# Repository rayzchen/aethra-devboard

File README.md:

# aethra-devboard
Custom devboard based on the RP2040 chip. Includes LiPo 3.7V battery charger and
power source selector, onboard neopixel LED, 16MB flash storage and 29 GPIO
pins.

## Schematic

## PCB

## BOM
|Comment                    |Footprint                                       |LCSC Part No|Quantity|Link                                                 |Price/unit |Total |
|---------------------------|------------------------------------------------|------------|--------|-----------------------------------------------------|-----------|------|
|AP2112K-3.3                |SOT-23-5                                        |C23380830   |1       |https://www.lcsc.com/product-detail/C23380830.html   |0.0975     |0.0975|
|RP2040                     |QFN-56-1EP_7x7mm_P0.4mm_EP3.2x3.2mm             |C2040       |1       |https://www.lcsc.com/product-detail/C2040.html       |0.9577     |0.9577|
|33pF                       |C_0402_1005Metric                               |C1562       |2       |https://www.lcsc.com/product-detail/C1562.html       |0.0011     |0.0022|
|0.1uF                      |C_0402_1005Metric                               |C1525       |11      |https://www.lcsc.com/product-detail/C1525.html       |0.0013     |0.0143|
|10K                        |R_0402_1005Metric                               |C25744      |4       |https://www.lcsc.com/product-detail/C25744.html      |0.0007     |0.0028|
|1uF                        |C_0402_1005Metric                               |C52923      |2       |https://www.lcsc.com/product-detail/C52923.html      |0.0032     |0.0064|
|1K                         |R_0402_1005Metric                               |C11702      |2       |https://www.lcsc.com/product-detail/C11702.html      |0.0006     |0.0012|
|Conn_01x02                 |JST_PH_S2B-PH-SM4-TB_1x02-1MP_P2.00mm_Horizontal|C295747     |1       |https://www.lcsc.com/product-detail/C295747.html     |0.1877     |0.1877|
|27                         |R_0402_1005Metric                               |C138021     |2       |https://www.lcsc.com/product-detail/C138021.html     |0.0008     |0.0016|
|12 MHz                     |Crystal_SMD_3225-4Pin_3.2x2.5mm                 |C9002       |1       |https://www.lcsc.com/product-detail/C9002.html       |0.0681     |0.0681|
|W25Q16JVZPIQ               |Winbond_USON-8-1EP_3x2mm_P0.5mm_EP0.2x1.6mm     |C377853     |1       |https://www.lcsc.com/product-detail/C377853.html     |1.0674     |1.0674|
|USB_C_Receptacle_USB2.0_14P|USB_C_Receptacle_HRO_TYPE-C-31-M-12             |C165948     |1       |https://www.lcsc.com/product-detail/C165948.html     |0.1772     |0.1772|
|LED                        |LED_0402_1005Metric                             |C130719     |1       |https://www.lcsc.com/product-detail/C130719.html     |0.0369     |0.0369|
|10uF                       |C_0402_1005Metric                               |C15525      |3       |https://www.lcsc.com/product-detail/C15525.html      |0.005      |0.015 |
|Conn_01x03                 |JST_SH_BM03B-SRSS-TB_1x03-1MP_P1.00mm_Vertical  |C160389     |1       |https://www.lcsc.com/product-detail/C160389.html     |0.2576     |0.2576|
|DMG2301L                   |SOT-23                                          |C102619     |1       |https://www.lcsc.com/product-detail/C102619.html     |0.07       |0.07  |
|5.1K                       |R_0402_1005Metric                               |C25905      |3       |https://www.lcsc.com/product-detail/C25905.html      |0.0006     |0.0018|
|MCP73831-2-OT              |SOT-23-5                                        |C424093     |1       |https://www.lcsc.com/product-detail/C424093.html     |0.7226     |0.7226|
|MBR0540                    |D_SOD-123                                       |C116159     |1       |https://www.lcsc.com/product-detail/C116159.html     |0.0204     |0.0204|
|SW_Push                    |SW_Push_SPST_NO_Alps_SKRK                       |C720477     |1       |https://www.lcsc.com/product-detail/C720477.html     |0.0444     |0.0444|
|Conn_01x20                 |PinHeader_1x20_P2.54mm_Vertical                 |            |2       |https://www.aliexpress.com/item/4001053521664.html   |1.255      |2.51  |
|SK6805                     |LED_SK6805_PLCC4_2.4x2.7mm_P1.3mm               |            |1       |https://www.aliexpress.com/item/1005008719791221.html|1.37       |1.37  |
|                           |                                                |            |        |                                                     |Grand Total|7.6328|

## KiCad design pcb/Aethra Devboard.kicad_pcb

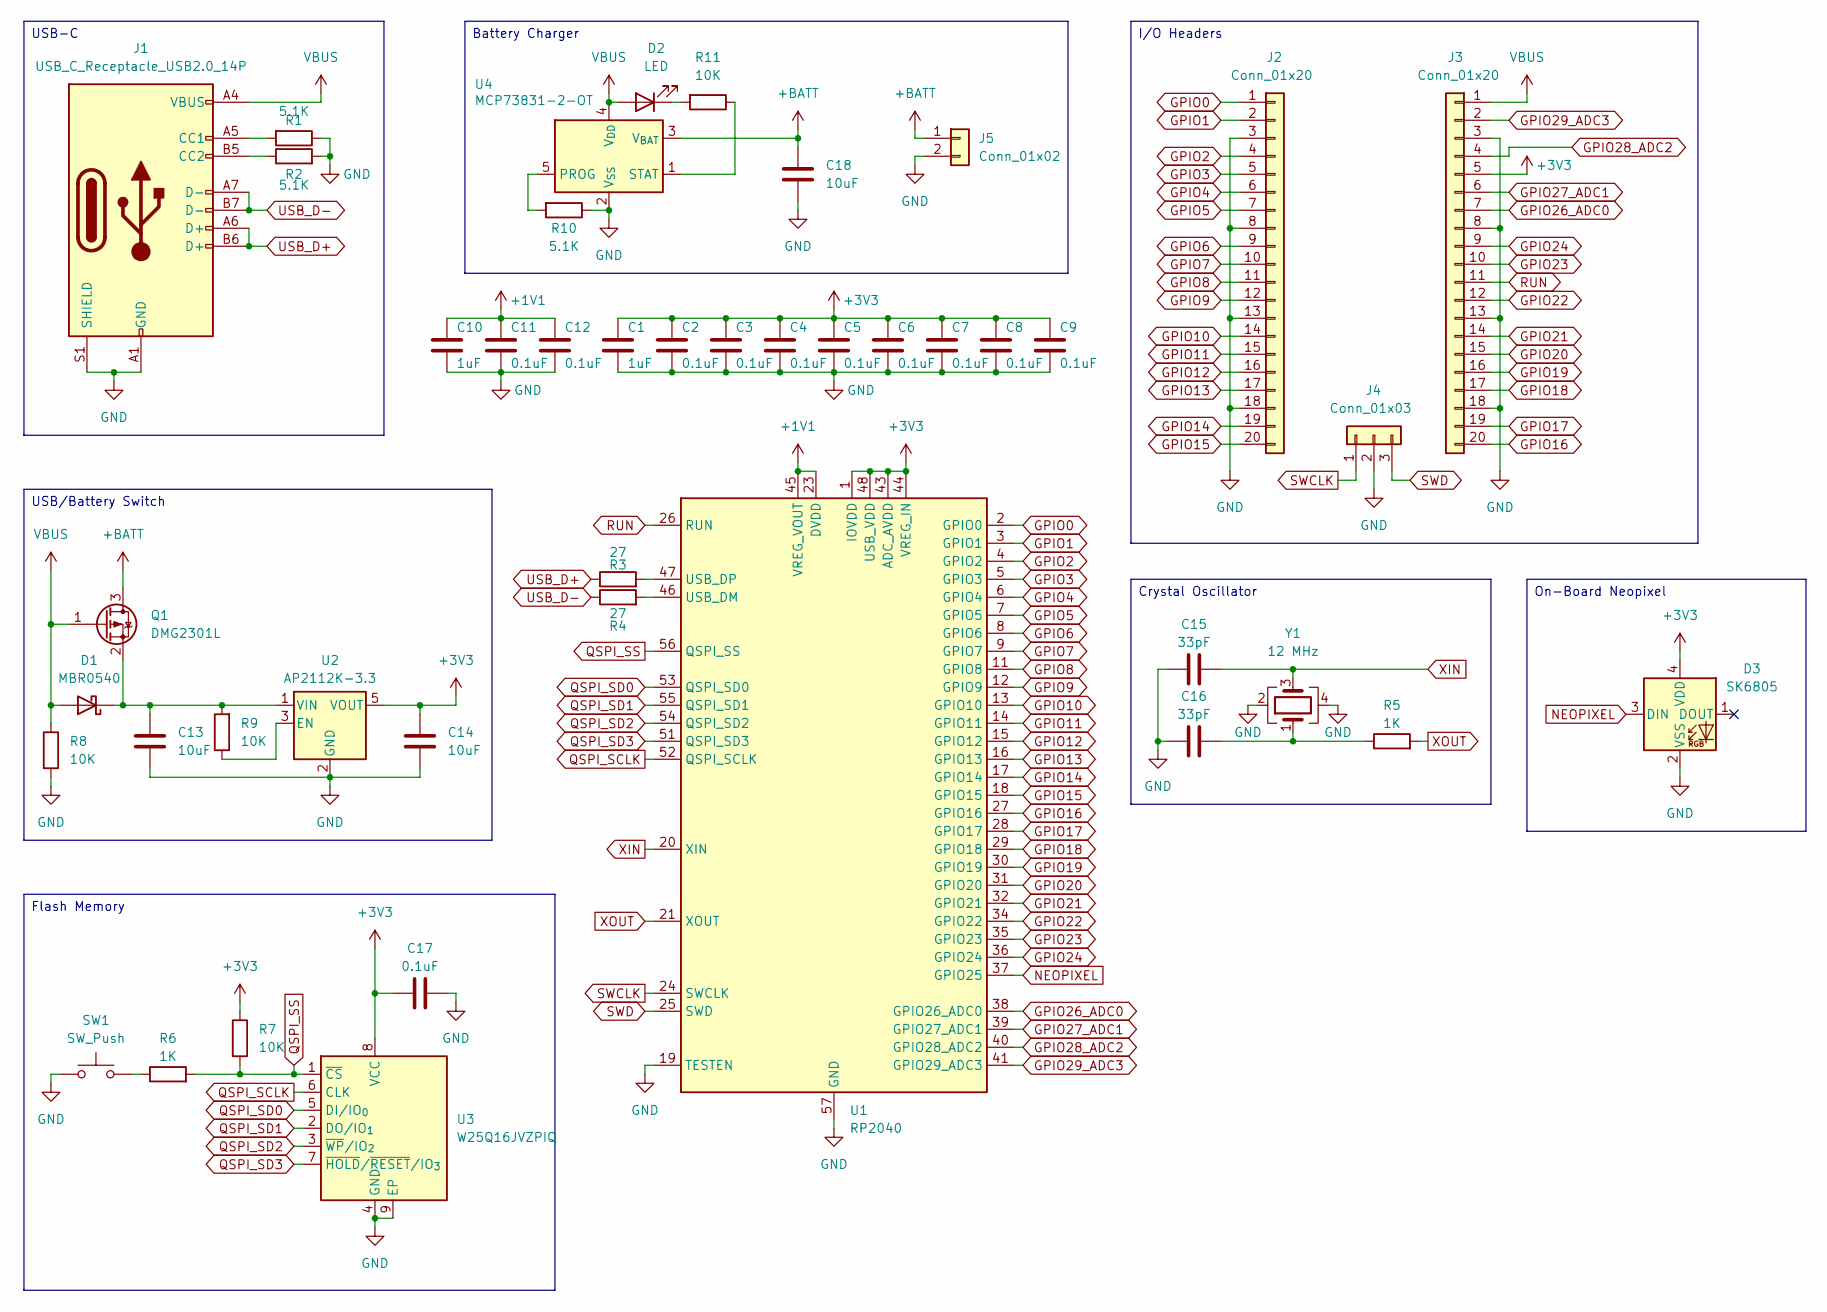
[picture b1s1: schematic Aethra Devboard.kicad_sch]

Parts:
C1, C10: 1uF; C_0402_1005Metric
C2, C3, C4, C5, C6, C7, C8, C9, C11, C12, C17: 0.1uF; C_0402_1005Metric
C13, C14, C18: 10uF; C_0402_1005Metric
C15, C16: 33pF; C_0402_1005Metric
D1: MBR0540; D_SOD-123
D2: LED; LED_0402_1005Metric
D3: SK6805; LED_SK6805_PLCC4_2.4x2.7mm_P1.3mm
J1: USB_C_Receptacle_USB2.0_14P; USB_C_Receptacle_HRO_TYPE-C-31-M-12
J2, J3: Conn_01x20; PinHeader_1x20_P2.54mm_Vertical
J4: Conn_01x03; JST_SH_BM03B-SRSS-TB_1x03-1MP_P1.00mm_Vertical
J5: Conn_01x02; JST_PH_S2B-PH-SM4-TB_1x02-1MP_P2.00mm_Horizontal
Q1: DMG2301L; SOT-23
R1, R2, R10: 5.1K; R_0402_1005Metric
R3, R4: 27; R_0402_1005Metric
R5, R6: 1K; R_0402_1005Metric
R7, R8, R9, R11: 10K; R_0402_1005Metric
SW1: SW_Push; SW_Push_SPST_NO_Alps_SKRK
U1: RP2040; QFN-56-1EP_7x7mm_P0.4mm_EP3.2x3.2mm
U2: AP2112K-3.3; SOT-23-5
U3: W25Q16JVZPIQ; Winbond_USON-8-1EP_3x2mm_P0.5mm_EP0.2x1.6mm
U4: MCP73831-2-OT; SOT-23-5
Y1: 12 MHz; Crystal_SMD_3225-4Pin_3.2x2.5mm

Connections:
+1V1: C10.1, C11.1, C12.1, U1.23 (DVDD), U1.45 (VREG_VOUT), U1.50 (DVDD)
+3V3: C1.1, C2.1, C3.1, C4.1, C5.1, C6.1, C7.1, C8.1, C9.1, C14.1, C17.1, D3.4 (VDD), J3.5, R7.1, U1.1 (IOVDD), U1.10 (IOVDD), U1.22 (IOVDD), U1.33 (IOVDD), U1.42 (IOVDD), U1.43 (ADC_AVDD), U1.44 (VREG_IN), U1.48 (USB_VDD), U1.49 (IOVDD), U2.5 (VOUT), U3.8 (VCC)
+BATT: C18.1, J5.1, Q1.3 (D), U4.3 (V_{BAT})
GND: C1.2, C2.2, C3.2, C4.2, C5.2, C6.2, C7.2, C8.2, C9.2, C10.2, C11.2, C12.2, C13.2, C14.2, C15.1, C16.1, C17.2, C18.2, D3.2 (VSS), J1.A1 (GND), J1.A12 (GND), J1.B1 (GND), J1.B12 (GND), J1.S1 (SHIELD), J2.3, J2.8, J2.13, J2.18, J3.3, J3.8, J3.13, J3.18, J4.2, J5.2, R1.1, R2.2, R8.2, R10.1, SW1.1, U1.19 (TESTEN), U1.57 (GND), U2.2 (GND), U3.4 (GND), U3.9 (EP), U4.2 (V_{SS}), Y1.2, Y1.4
GPIO0: J2.1, U1.2 (GPIO0)
GPIO1: J2.2, U1.3 (GPIO1)
GPIO2: J2.4, U1.4 (GPIO2)
GPIO3: J2.5, U1.5 (GPIO3)
GPIO4: J2.6, U1.6 (GPIO4)
GPIO5: J2.7, U1.7 (GPIO5)
GPIO6: J2.9, U1.8 (GPIO6)
GPIO7: J2.10, U1.9 (GPIO7)
GPIO8: J2.11, U1.11 (GPIO8)
GPIO9: J2.12, U1.12 (GPIO9)
GPIO10: J2.14, U1.13 (GPIO10)
GPIO11: J2.15, U1.14 (GPIO11)
GPIO12: J2.16, U1.15 (GPIO12)
GPIO13: J2.17, U1.16 (GPIO13)
GPIO14: J2.19, U1.17 (GPIO14)
GPIO15: J2.20, U1.18 (GPIO15)
GPIO16: J3.20, U1.27 (GPIO16)
GPIO17: J3.19, U1.28 (GPIO17)
GPIO18: J3.17, U1.29 (GPIO18)
GPIO19: J3.16, U1.30 (GPIO19)
GPIO20: J3.15, U1.31 (GPIO20)
GPIO21: J3.14, U1.32 (GPIO21)
GPIO22: J3.12, U1.34 (GPIO22)
GPIO23: J3.10, U1.35 (GPIO23)
GPIO24: J3.9, U1.36 (GPIO24)
GPIO26_ADC0: J3.7, U1.38 (GPIO26_ADC0)
GPIO27_ADC1: J3.6, U1.39 (GPIO27_ADC1)
GPIO28_ADC2: J3.4, U1.40 (GPIO28_ADC2)
GPIO29_ADC3: J3.2, U1.41 (GPIO29_ADC3)
NEOPIXEL: D3.3 (DIN), U1.37 (GPIO25)
unnamed: C16.2, R5.1, Y1.1
unnamed: C13.1, D1.1 (K), Q1.2 (S), R9.2, U2.1 (VIN)
unnamed: D2.1 (K), R11.2
unnamed: J1.A5 (CC1), R1.2
unnamed: J1.B5 (CC2), R2.1
unnamed: R6.1, SW1.2
unnamed: R4.2, U1.46 (USB_DM)
unnamed: R3.2, U1.47 (USB_DP)
unnamed: R9.1, U2.3 (EN)
unnamed: R10.2, U4.5 (PROG)
unnamed: R11.1, U4.1 (STAT)
QSPI_SCLK: U1.52 (QSPI_SCLK), U3.6 (CLK)
QSPI_SD0: U1.53 (QSPI_SD0), U3.5 (DI/IO_{0})
QSPI_SD1: U1.55 (QSPI_SD1), U3.2 (DO/IO_{1})
QSPI_SD2: U1.54 (QSPI_SD2), U3.3 (~WP/IO_{2})
QSPI_SD3: U1.51 (QSPI_SD3), U3.7 (~HOLD/~RESET/IO_{3})
QSPI_SS: R6.2, R7.2, U1.56 (QSPI_SS), U3.1 (~CS)
RUN: J3.11, U1.26 (RUN)
SWCLK: J4.1, U1.24 (SWCLK)
SWD: J4.3, U1.25 (SWD)
USB_D+: J1.A6 (D+), J1.B6 (D+), R3.1
USB_D-: J1.A7 (D-), J1.B7 (D-), R4.1
VBUS: D1.2 (A), D2.2 (A), J1.A4 (VBUS), J1.A9 (VBUS), J1.B4 (VBUS), J1.B9 (VBUS), J3.1, Q1.1 (G), R8.1, U4.4 (V_{DD})
XIN: C15.2, U1.20 (XIN), Y1.3
XOUT: R5.2, U1.21 (XOUT)

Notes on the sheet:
USB/Battery Switch
I/O Headers
Crystal Oscillator
Battery Charger
Flash Memory
USB-C
On-Board Neopixel

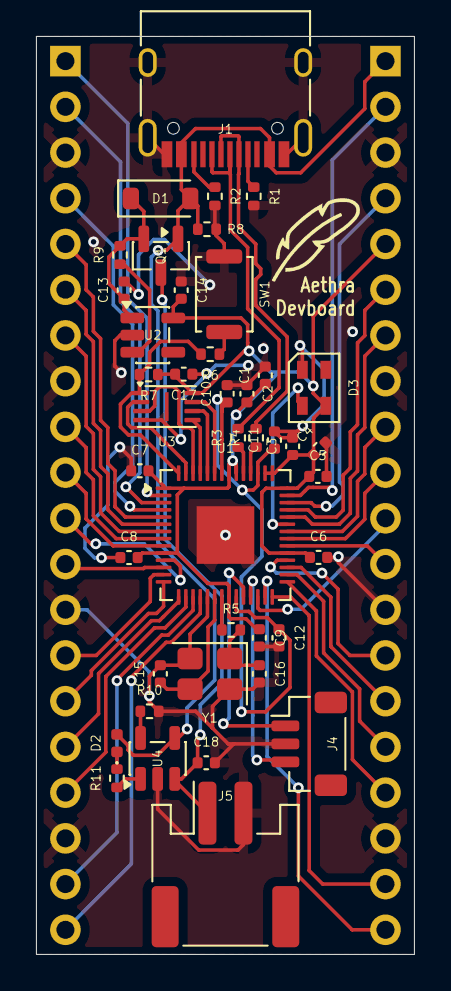
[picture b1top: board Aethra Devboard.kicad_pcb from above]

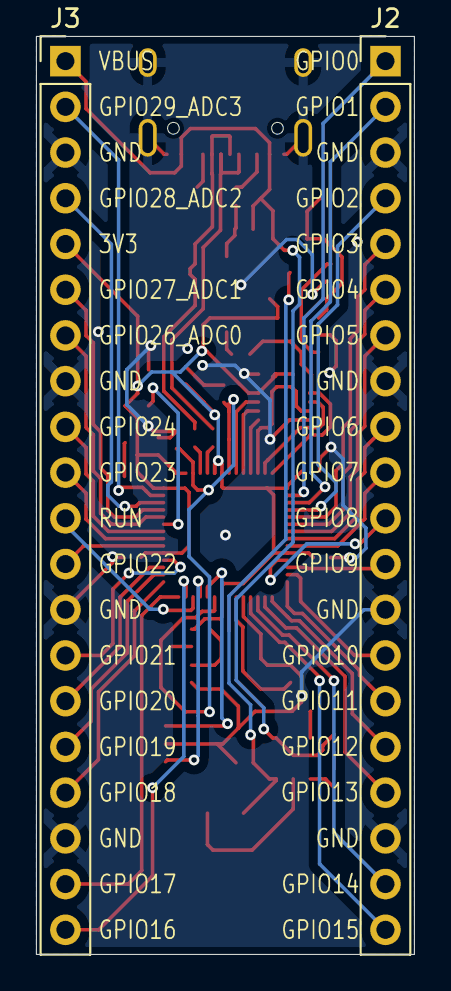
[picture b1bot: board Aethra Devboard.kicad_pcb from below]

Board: 2 copper layers, 21.0 x 51.0 mm, 44 parts (2 on the bottom side), 59 nets.

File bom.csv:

Comment,Designator,Footprint,LCSC Part No,Quantity,Link,Price/unit,Total
AP2112K-3.3,U2,SOT-23-5,C23380830,1,https://www.lcsc.com/product-detail/C23380830.html,0.0975,0.0975
RP2040,U1,QFN-56-1EP_7x7mm_P0.4mm_EP3.2x3.2mm,C2040,1,https://www.lcsc.com/product-detail/C2040.html,0.9577,0.9577
33pF,"C15,C16",C_0402_1005Metric,C1562,2,https://www.lcsc.com/product-detail/C1562.html,0.0011,0.0022
0.1uF,"C6,C5,C3,C2,C11,C8,C17,C9,C12,C7,C4",C_0402_1005Metric,C1525,11,https://www.lcsc.com/product-detail/C1525.html,0.0013,0.0143
10K,"R9,R11,R8,R7",R_0402_1005Metric,C25744,4,https://www.lcsc.com/product-detail/C25744.html,0.0007,0.0028
1uF,"C1,C10",C_0402_1005Metric,C52923,2,https://www.lcsc.com/product-detail/C52923.html,0.0032,0.0064
1K,"R5,R6",R_0402_1005Metric,C11702,2,https://www.lcsc.com/product-detail/C11702.html,0.0006,0.0012
Conn_01x02,J5,JST_PH_S2B-PH-SM4-TB_1x02-1MP_P2.00mm_Horizontal,C295747,1,https://www.lcsc.com/product-detail/C295747.html,0.1877,0.1877
27,"R3,R4",R_0402_1005Metric,C138021,2,https://www.lcsc.com/product-detail/C138021.html,0.0008,0.0016
12 MHz,Y1,Crystal_SMD_3225-4Pin_3.2x2.5mm,C9002,1,https://www.lcsc.com/product-detail/C9002.html,0.0681,0.0681
W25Q16JVZPIQ,U3,Winbond_USON-8-1EP_3x2mm_P0.5mm_EP0.2x1.6mm,C377853,1,https://www.lcsc.com/product-detail/C377853.html,1.0674,1.0674
USB_C_Receptacle_USB2.0_14P,J1,USB_C_Receptacle_HRO_TYPE-C-31-M-12,C165948,1,https://www.lcsc.com/product-detail/C165948.html,0.1772,0.1772
LED,D2,LED_0402_1005Metric,C130719,1,https://www.lcsc.com/product-detail/C130719.html,0.0369,0.0369
10uF,"C14,C13,C18",C_0402_1005Metric,C15525,3,https://www.lcsc.com/product-detail/C15525.html,0.005,0.015
Conn_01x03,J4,JST_SH_BM03B-SRSS-TB_1x03-1MP_P1.00mm_Vertical,C160389,1,https://www.lcsc.com/product-detail/C160389.html,0.2576,0.2576
DMG2301L,Q1,SOT-23,C102619,1,https://www.lcsc.com/product-detail/C102619.html,0.07,0.07
5.1K,"R10,R1,R2",R_0402_1005Metric,C25905,3,https://www.lcsc.com/product-detail/C25905.html,0.0006,0.0018
MCP73831-2-OT,U4,SOT-23-5,C424093,1,https://www.lcsc.com/product-detail/C424093.html,0.7226,0.7226
MBR0540,D1,D_SOD-123,C116159,1,https://www.lcsc.com/product-detail/C116159.html,0.0204,0.0204
SW_Push,SW1,SW_Push_SPST_NO_Alps_SKRK,C720477,1,https://www.lcsc.com/product-detail/C720477.html,0.0444,0.0444
Conn_01x20,"J2,J3",PinHeader_1x20_P2.54mm_Vertical,,2,https://www.aliexpress.com/item/4001053521664.html,1.255,2.51
SK6805,D3,LED_SK6805_PLCC4_2.4x2.7mm_P1.3mm,,1,https://www.aliexpress.com/item/1005008979678361.html,5.53,5.53
LiPo,BATT,LiPoly 3.7V 2000mAh PH2.0,,1,https://www.aliexpress.com/item/1005009590723370.html,1.53,1.53
,,,,,,Grand Total,13.3228

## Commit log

2026-01-22 First draft of schematic
2026-01-24 Move kicad files to correct location
2026-01-25 Add footprints to components
2026-01-25 Start routing of PCB
2026-01-25 Finish routing PCB
2026-01-25 Add 3d models to viewer
2026-01-25 Add pinouts and icon to silkscreen
2026-01-25 Add BOM
2026-01-26 Reroute PCB
2026-01-26 Correct BOM
